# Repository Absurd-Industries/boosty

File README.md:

# Boosty  [WIP!]

**Need 5V at up to 5A from 3.7V batteries? You need a Boosty!**

A super accessible, pill-shaped boost converter breakout board for anyone who needs a boost. Designed by [Absurd Industries](https://absurdindustries.in) - open power electronics for everyone!

Boosty takes a single-cell lithium battery (3.0–4.2V) and boosts it to a rock-solid 5V rail capable of delivering serious current. Born out of the need to power 200 WS2812B LEDs on the [Supersaber](https://github.com/Absurd-Industries/supersaber) without praying to the thermal gods.

## Specs

| Parameter | Value |
|-----------|-------|
| Input voltage | 3.0–4.2V (single-cell Li-ion / LiPo) |
| Output voltage | 5.0V regulated |
| Max output current | 5A continuous |
| Peak switch current | 10A (with cycle-by-cycle protection) |
| Efficiency | ~90% typical at 2A load |
| Switching frequency | ~600 kHz |
| Light-load mode | PFM (auto power-save) |
| Protections | OVP, OCP, thermal shutdown, UVLO |
| Board shape | Pill-shaped breakout |
| Converter IC | TPS61088RHLT (Texas Instruments) |
| License | CERN-OHL-S v2 (copyleft) |

## When to use Boosty

- Powering addressable LED strips (WS2812B, SK6812, APA102) from a single Li-ion cell
- Portable USB power banks and charging circuits
- Raspberry Pi / SBC projects running on battery
- Any project that needs 5V and more current than those tiny SOT-23 boost converters can handle
- When your existing boost converter is running at 2.5x its rated current and you've been getting away with it (you know who you are)

## Schematic

Based on the TPS61088 typical application circuit adapted for 5V output from a single-cell lithium battery.

### Bill of materials

| Ref | Value | Package | Description |
|-----|-------|---------|-------------|
| U1 | TPS61088RHLT | VQFN-20 | Synchronous boost converter |
| L1 | 2.2 µH | — | Power inductor, 12A+ saturation (Cyntec PIMB065T-2R2MS or equivalent) |
| C1, C2, C3 | 22 µF | 0805/1206 | Ceramic X5R, 10V min — input bulk capacitors |
| C4, C5, C6 | 22 µF | 0805/1206 | Ceramic X5R, 10V min — output bulk capacitors |
| C7 | 0.1 µF | 0402/0603 | Ceramic — VIN pin bypass (place closest to pin) |
| C8 | 2.2 µF | 0402/0603 | Ceramic — VCC internal LDO cap |
| C9 | 0.1 µF | 0402/0603 | Ceramic — BOOT cap (BOOT to SW) |
| C10 | 47 nF | 0402/0603 | Ceramic — soft-start cap |
| C11 | 4.7 nF | 0402/0603 | Ceramic C0G — compensation cap |
| R1 | 178 kΩ | 0402/0603 | 1% — FB divider top (sets VOUT = 5.03V) |
| R2 | 56 kΩ | 0402/0603 | 1% — FB divider bottom |
| R3 | 270 kΩ | 0402/0603 | 1% — switching frequency set (~600 kHz) |
| R4 | 100 kΩ | 0402/0603 | 1% — current limit set (11.9A peak) |
| R5 | 10 kΩ | 0402/0603 | 1% — compensation resistor |
| SW1 | — | — | SPST toggle/slide switch (EN to VBAT) |

### Key connections

- **EN** → SPST switch → VBAT (hardware power control; or tie directly to VBAT for always-on)
- **FB** → midpoint of R1/R2 divider from VOUT to GND
- **FSW** → R3 → SW node (not ground!)
- **ILIM** → R4 → AGND
- **COMP** → R5 + C11 → AGND
- **SS** → C10 → GND
- **VCC** → C8 → GND
- **MODE** → float (PFM mode for light-load efficiency)
- **NC pins (11, 12)** → GND (thermal dissipation)
- **Thermal pad** → GND with thermal vias

## PCB layout [WIP]

**Page 23 of datasheets/TPS61088.PDF**

- Need to keep SW traces **short and wide** — this is the high-frequency switching node
- Place input caps (C1–C3) as close to VIN pin as possible
- Place output caps (C4–C6) as close to VOUT pins as possible
- C7 (0.1µF VIN bypass) should be the **closest** cap to the VIN pin
- Use a solid ground plane on the bottom layer
- Stitch the thermal pad to the ground plane with **multiple thermal vias** (at least 6–9 vias under the pad)
- Keep AGND and PGND connected at the IC but avoid routing noisy power currents through the analog ground path
- R1/R2 feedback divider should route cleanly to FB without crossing the SW node

## DC bias derating warning

Ceramic capacitors lose capacitance under DC bias. A 22µF 0805 X5R cap rated at 6.3V might only give you 12–15µF at 5V. Use **10V rated** capacitors (or higher) to maintain adequate effective capacitance. Check the manufacturer's DC bias curves for your specific caps.

## Design calculations

All calculations derived from the TPS61088 datasheet (SLVSCM8D, Rev D, August 2021).

**Output voltage** (Equation 7):
```
VOUT = VREF × (1 + R1/R2) = 1.204 × (1 + 178/56) = 5.03V
```

**Switching frequency** (Equation 5, at VIN = 3.6V):
```
RFREQ = 4 × (1/fSW - tDELAY × VOUT/VIN) / CFREQ ≈ 270 kΩ → ~600 kHz
```

**Current limit** (Equation 6, PFM mode):
```
ILIM = 1,190,000 / RILIM = 1,190,000 / 100,000 = 11.9A peak
```

**Soft-start time** (Equation 1):
```
tSS = VREF × CSS / ISS = 1.204 × 47nF / 5µA ≈ 11.3 ms
```

## Firmware power budgeting (optional but recommended)

If you're driving LEDs, consider adding a software current budget to protect the converter from accidental overload:

```python
MAX_MA = 4000  # safe continuous output budget

def safe_brightness(color, num_leds, max_ma):
    r, g, b = color
    ma_per_led = ((r / 255) + (g / 255) + (b / 255)) * 20
    total_at_full = ma_per_led * num_leds
    if total_at_full == 0:
        return 1.0
    return min(max_ma / total_at_full, 1.0)
```

This way your firmware automatically dims brighter colors to stay within the power budget. Open hardware with a seatbelt.

## What Boosty replaced

The Supersaber's original boost converter was a TPS61032 (4A switch, ~800mA rated output). It was being operated at roughly 2.5x its rated capacity through a combination of optimism and thermal luck. Boosty replaces that with a TPS61088 that has actual headroom — 10A switch current, synchronous rectification, and proper thermal management.

| | TPS61032 (old) | TPS61088 (Boosty) |
|-|----------------|-------------------|
| Switch current | 4A | 10A |
| Rated output @ 5V | ~800 mA | ~5A |
| Synchronous | No | Yes |
| Efficiency @ 2A | ~82% | ~90% |
| Running gold LEDs | 😓 redline | 😌 cruising |

## License

This project is licensed under **CERN-OHL-S v2** (CERN Open Hardware Licence, Strongly Reciprocal). You are free to use, modify, and distribute this design, provided that any modifications are shared under the same license.

## Contributing

Found a bug? Want to improve the layout? Have a better inductor recommendation? Open an issue or PR. This is community hardware — your contributions make it better for everyone.

## Credits

⚔️ Designed by [Absurd Industries](https://absurdindustries.in) — copyleft consumer electronics, repairable by design, documented for humans.

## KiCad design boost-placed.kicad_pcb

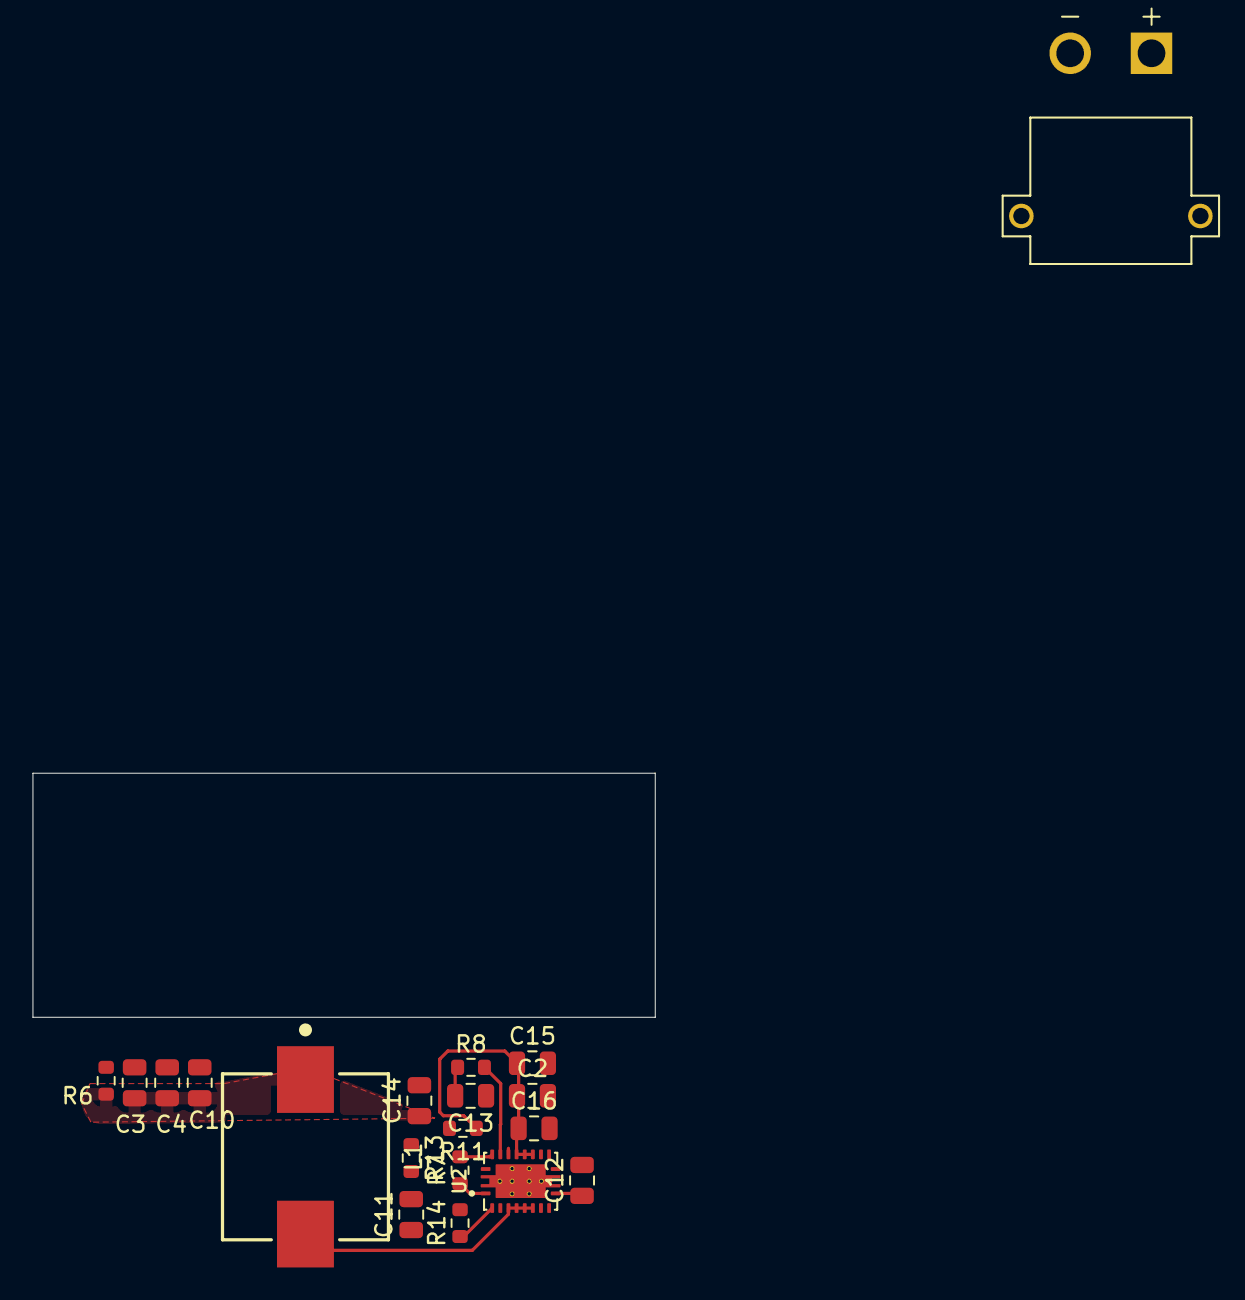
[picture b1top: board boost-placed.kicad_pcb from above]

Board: 2 copper layers, 38.2 x 15.0 mm, 19 parts (0 on the bottom side), 14 nets.

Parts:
C2, C3, C4, C15, C16: 22uF; C_0805_2012Metric
C10, C14: 0.1uF; C_0805_2012Metric
C11: 2.2uF; C_0805_2012Metric
C12: 47nF; C_0805_2012Metric
C13: 4.7nF; C_0805_2012Metric
L1: 2.2uH; WE-LHMI_1040
R6: 270k; R_0603_1608Metric
R7: 100k; R_0603_1608Metric
R8: 10k; R_0603_1608Metric
R11: 178k; R_0603_1608Metric
R13: 56k; R_0603_1608Metric
R14: 470k; R_0603_1608Metric
SW1: SW_SPST; AMASS_XT30PW-M
U2: TPS61088RHLT; IC_MSP430FR2522IRHLR

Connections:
+5V: C2.1, C15.1, C16.1, R11.1, U2.14 (VOUT), U2.15 (VOUT), U2.16 (VOUT)
GND: C2.2, C3.1, C4.1, C11.2, C12.2, C13.1, C15.2, C16.2, R13.1, R14.2, U2.13 (MODE), U2.20 (AGND), U2.21 (PGND)
unnamed: C13.2, R8.1
unnamed: L1.2, U2.4 (SW), U2.5 (SW), U2.6 (SW), U2.7 (SW)
unnamed: R14.1, U2.2 (EN)
unnamed: C10.2, U2.8 (BOOT)
unnamed: R8.2, U2.18 (COMP)
unnamed: R11.2, R13.2, U2.17 (FB)
unnamed: R6.2, U2.3 (FSW)
unnamed: R7.2, U2.19 (ILIM)
unnamed: C12.1, U2.10 (SS)
unnamed: C11.1, R7.1, U2.1 (VCC)
unnamed: C14.2, U2.9 (VIN)
VBAT: C3.2, C4.2, C10.1, C14.1, L1.1, R6.1

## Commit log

2026-06-04 Boosty v0.
2026-06-04 Create README.md for Boosty boost converter
    Add detailed documentation for Boosty boost converter including specifications, usage scenarios, schematic, and design calculations.
2026-06-04 Add image to README for Boosty product
    Added an image to enhance the README content.
2026-06-04 Update PCB layout reference in README
2026-06-04 Added datasheets.
2026-06-05 feat: updated gitignore to have files not required to be version controlled
